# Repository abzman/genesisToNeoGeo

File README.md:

# genesisToNeoGeo
adapts genesis controllers to the neo geo

This can also be used to simulate button presses where an input pin needs to be grounded on any system.  It uses the MCP23018 as an open drain I/O expander to simulate mechanical buttons on those lines connecting to ground.

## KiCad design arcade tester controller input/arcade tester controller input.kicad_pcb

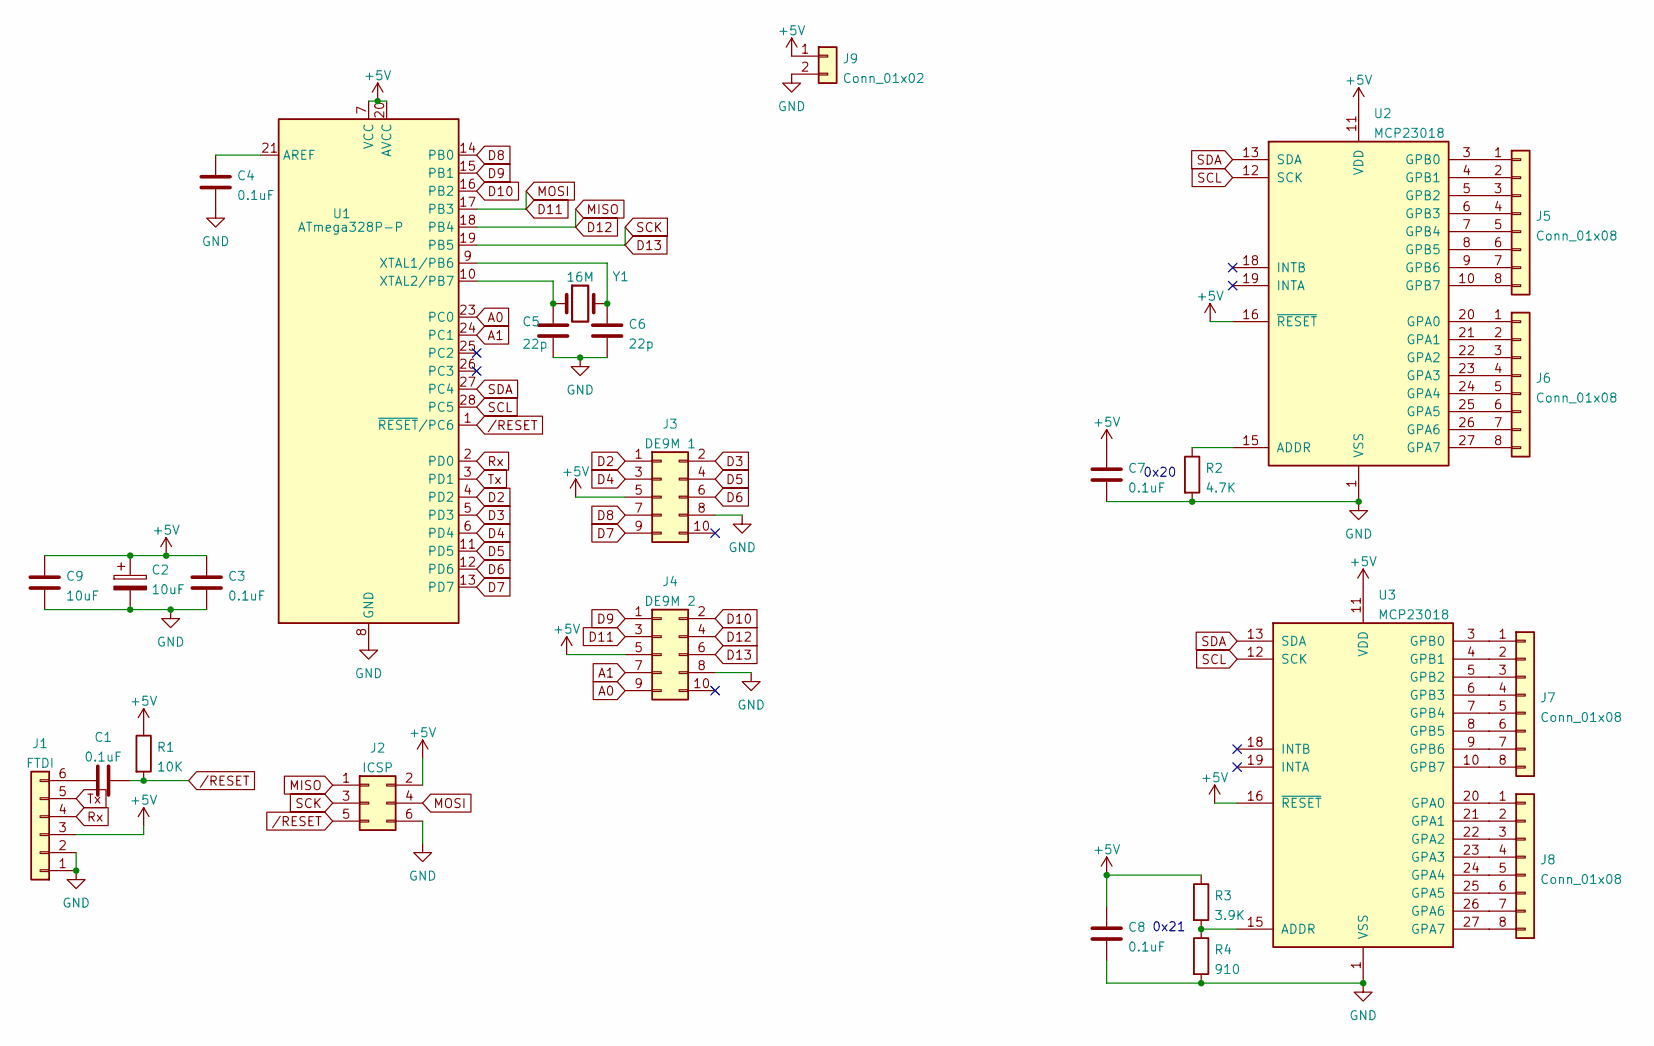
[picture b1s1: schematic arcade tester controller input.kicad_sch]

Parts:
C1, C3, C4, C7, C8: 0.1uF; C_0603_1608Metric
C2, C9: 10uF; C_0603_1608Metric
C5, C6: 22p; C_0603_1608Metric
J1: FTDI; PinHeader_1x06_P2.54mm_Vertical
J2: ICSP; PinHeader_2x03_P2.54mm_Vertical
J3: DE9M 1; PinHeader_2x05_P2.54mm_Vertical
J4: DE9M 2; PinHeader_2x05_P2.54mm_Vertical
J5, J6, J7, J8: Conn_01x08; PhoenixContact_MC_1,5_8-G-3.81_1x08_P3.81mm_Horizontal
J9: Conn_01x02; PhoenixContact_MC_1,5_2-G-3.81_1x02_P3.81mm_Horizontal
R1: 10K; R_Axial_DIN0204_L3.6mm_D1.6mm_P1.90mm_Vertical
R2: 4.7K; R_Axial_DIN0204_L3.6mm_D1.6mm_P1.90mm_Vertical
R3: 3.9K; R_Axial_DIN0204_L3.6mm_D1.6mm_P1.90mm_Vertical
R4: 910; R_Axial_DIN0204_L3.6mm_D1.6mm_P1.90mm_Vertical
U1: ATmega328P-P; DIP-28_W7.62mm
U2, U3: MCP23018; DIP-28_W7.62mm
Y1: 16M; Crystal_HC49-U_Vertical

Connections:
+5V: C2.1, C3.1, C7.1, C8.1, C9.1, J1.3, J2.2, J3.5, J4.5, J9.1, R1.1, R3.1, U1.7 (VCC), U1.20 (AVCC), U2.11 (VDD), U2.16 (~RESET), U3.11 (VDD), U3.16 (~RESET)
A0: J4.9, U1.23 (PC0)
A1: J4.7, U1.24 (PC1)
D2: J3.1, U1.4 (PD2)
D3: J3.2, U1.5 (PD3)
D4: J3.3, U1.6 (PD4)
D5: J3.4, U1.11 (PD5)
D6: J3.6, U1.12 (PD6)
D7: J3.9, U1.13 (PD7)
D8: J3.7, U1.14 (PB0)
D9: J4.1, U1.15 (PB1)
D10: J4.2, U1.16 (PB2)
D11: J2.4, J4.3, U1.17 (PB3)
D12: J2.1, J4.4, U1.18 (PB4)
D13: J2.3, J4.6, U1.19 (PB5)
GND: C2.2, C3.2, C4.2, C5.2, C6.2, C7.2, C8.2, C9.2, J1.1, J1.2, J2.6, J3.8, J4.8, J9.2, R2.2, R4.2, U1.8 (GND), U1.22 (GND), U2.1 (VSS), U3.1 (VSS)
unnamed: C1.1, J1.6
unnamed: C4.1, U1.21 (AREF)
unnamed: C5.1, U1.10 (XTAL2/PB7), Y1.1
unnamed: C6.1, U1.9 (XTAL1/PB6), Y1.2
unnamed: J5.1, U2.3 (GPB0)
unnamed: J5.2, U2.4 (GPB1)
unnamed: J5.3, U2.5 (GPB2)
unnamed: J5.4, U2.6 (GPB3)
unnamed: J5.5, U2.7 (GPB4)
unnamed: J5.6, U2.8 (GPB5)
unnamed: J5.7, U2.9 (GPB6)
unnamed: J5.8, U2.10 (GPB7)
unnamed: J6.1, U2.20 (GPA0)
unnamed: J6.2, U2.21 (GPA1)
unnamed: J6.3, U2.22 (GPA2)
unnamed: J6.4, U2.23 (GPA3)
unnamed: J6.5, U2.24 (GPA4)
unnamed: J6.6, U2.25 (GPA5)
unnamed: J6.7, U2.26 (GPA6)
unnamed: J6.8, U2.27 (GPA7)
unnamed: J7.1, U3.3 (GPB0)
unnamed: J7.2, U3.4 (GPB1)
unnamed: J7.3, U3.5 (GPB2)
unnamed: J7.4, U3.6 (GPB3)
unnamed: J7.5, U3.7 (GPB4)
unnamed: J7.6, U3.8 (GPB5)
unnamed: J7.7, U3.9 (GPB6)
unnamed: J7.8, U3.10 (GPB7)
unnamed: J8.1, U3.20 (GPA0)
unnamed: J8.2, U3.21 (GPA1)
unnamed: J8.3, U3.22 (GPA2)
unnamed: J8.4, U3.23 (GPA3)
unnamed: J8.5, U3.24 (GPA4)
unnamed: J8.6, U3.25 (GPA5)
unnamed: J8.7, U3.26 (GPA6)
unnamed: J8.8, U3.27 (GPA7)
unnamed: R2.1, U2.15 (ADDR)
unnamed: R3.2, R4.1, U3.15 (ADDR)
Rx: J1.4, U1.2 (PD0)
SCL: U1.28 (PC5), U2.12 (SCK), U3.12 (SCK)
SDA: U1.27 (PC4), U2.13 (SDA), U3.13 (SDA)
Tx: J1.5, U1.3 (PD1)
/RESET: C1.2, J2.5, R1.2, U1.1 (~RESET/PC6)

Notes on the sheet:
0x21
0x20

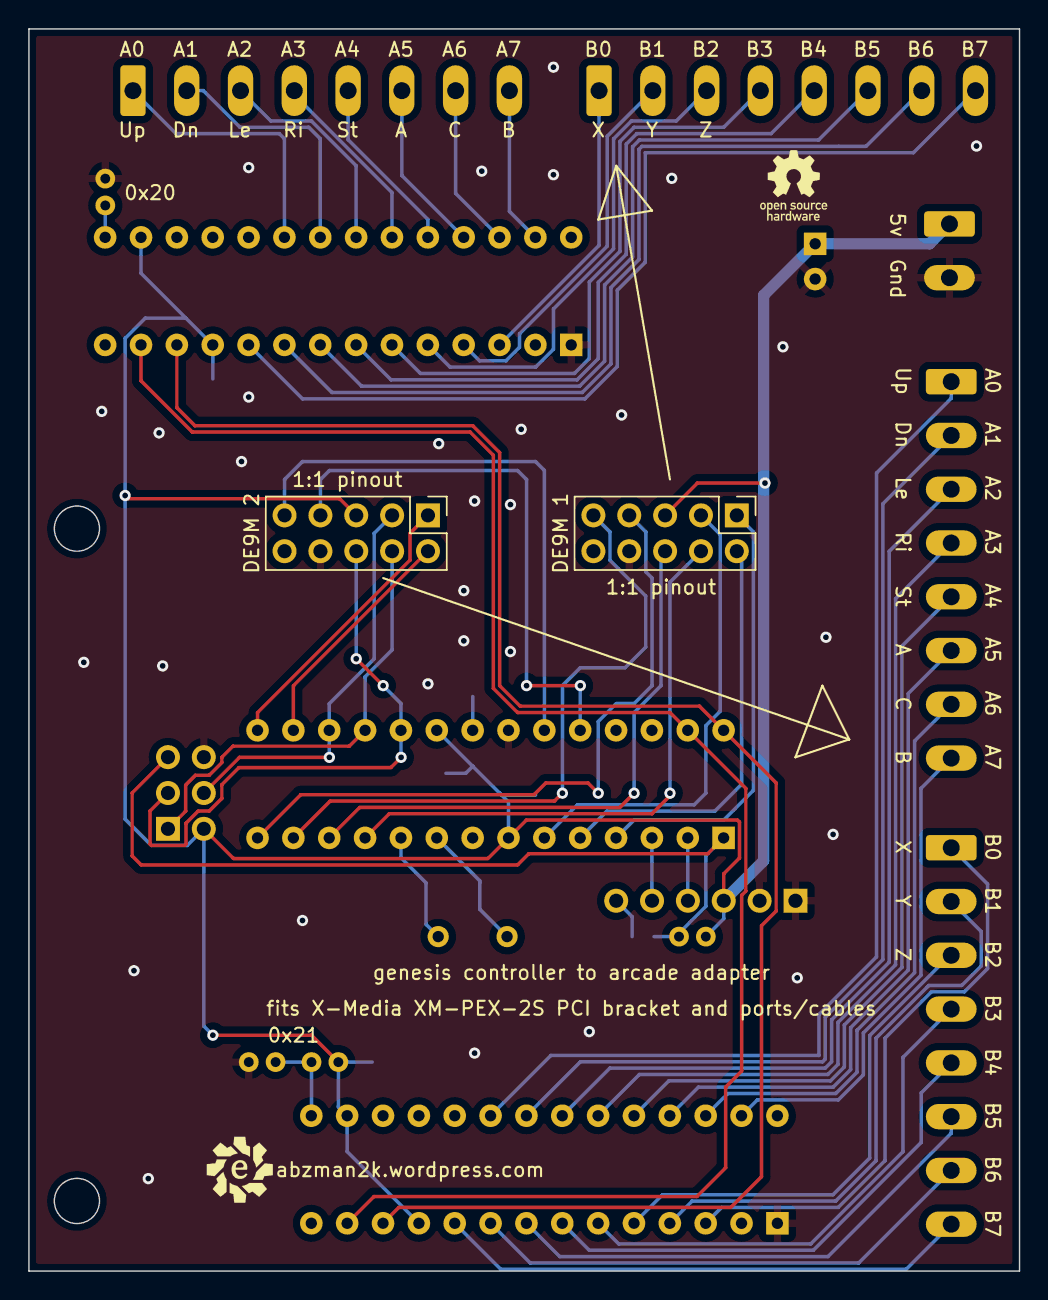
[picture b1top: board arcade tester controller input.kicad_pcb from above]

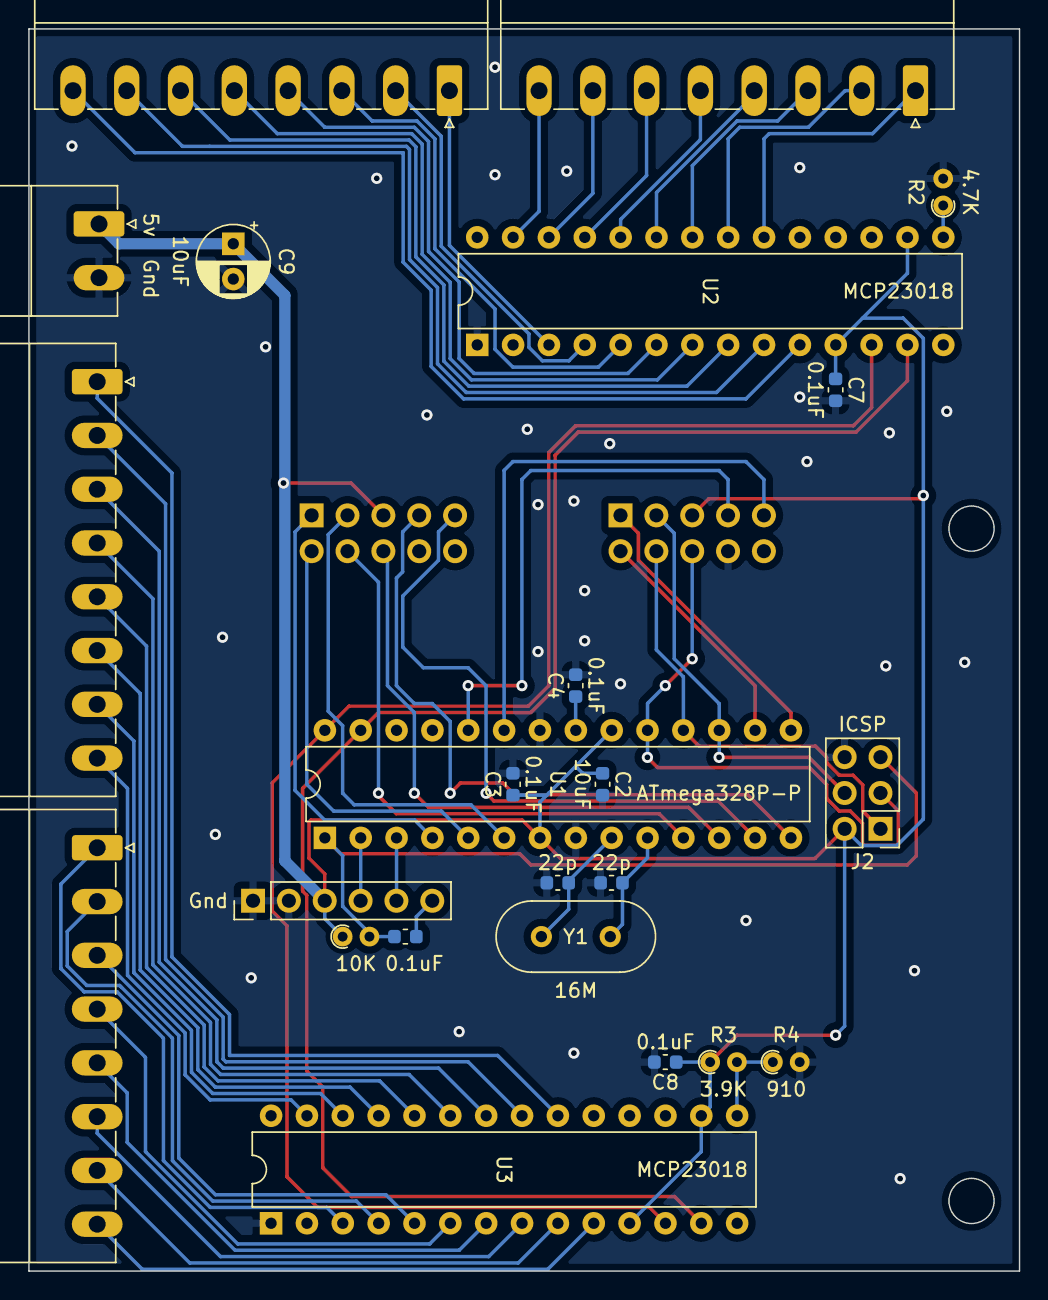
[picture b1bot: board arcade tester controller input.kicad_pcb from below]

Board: 2 copper layers, 70.2 x 88.0 mm, 26 parts (24 on the bottom side), 59 nets.

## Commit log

2021-04-16 first version
    it works
2022-10-24 added board layout to mount on PCI bracket
2022-11-23 made pcb for pci bracket board
2022-11-24 added 5v and gnd to controller ports
